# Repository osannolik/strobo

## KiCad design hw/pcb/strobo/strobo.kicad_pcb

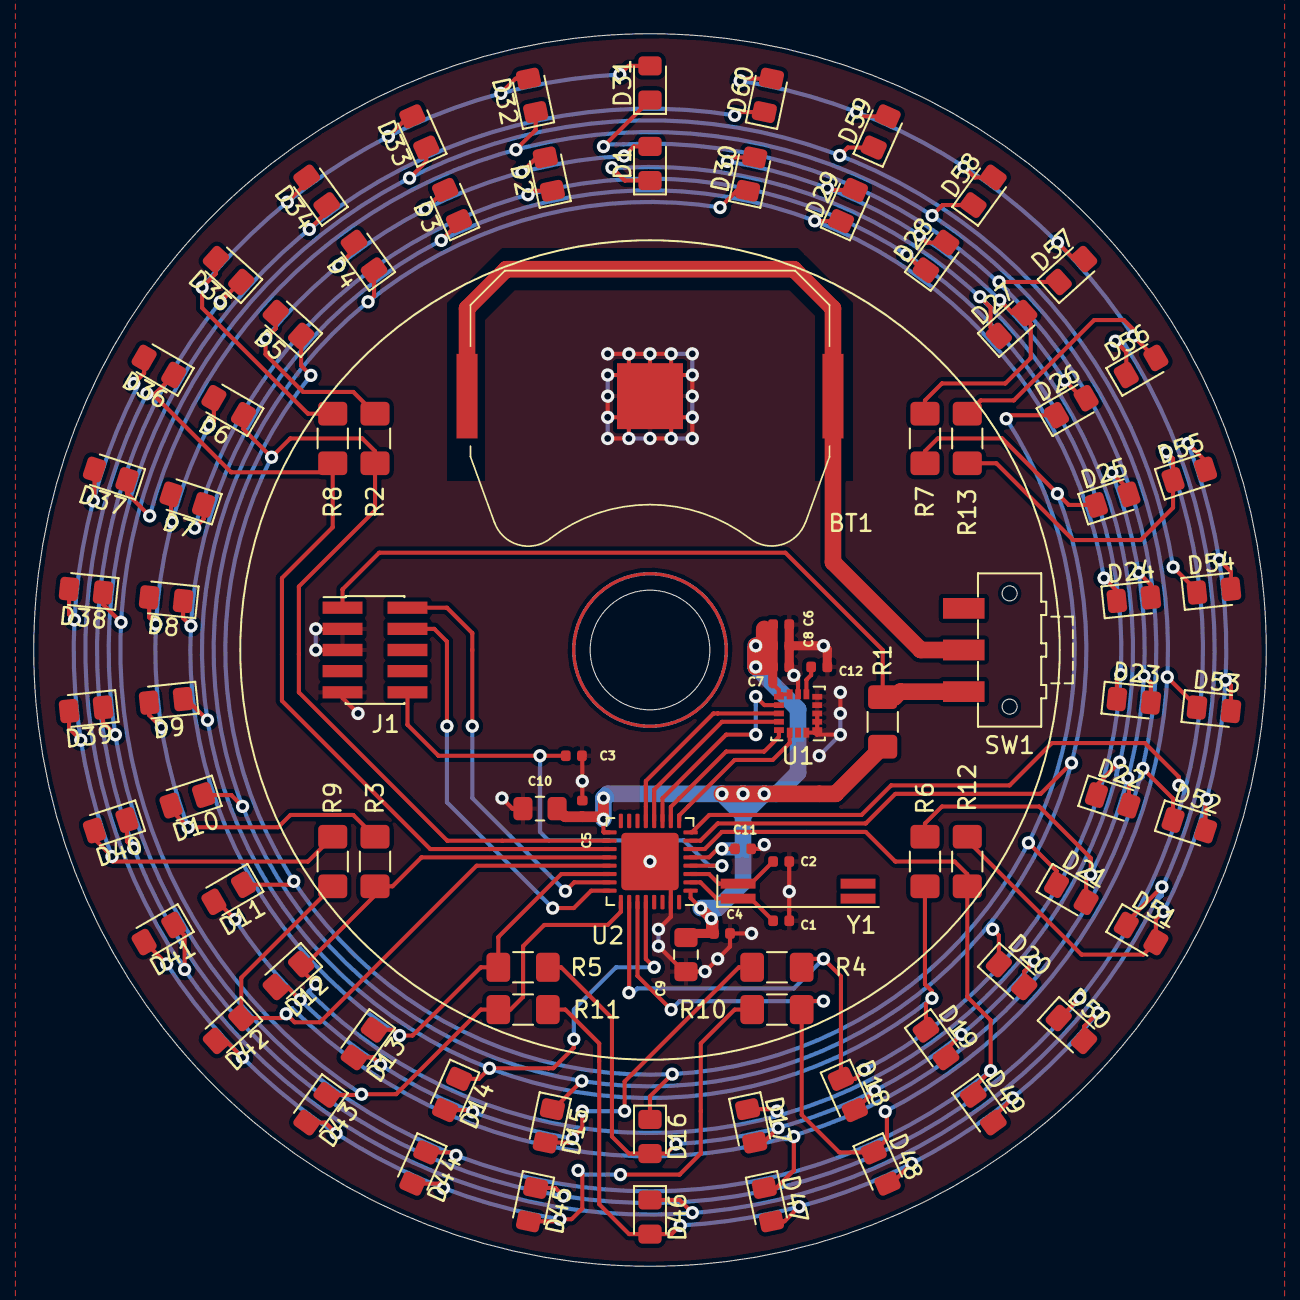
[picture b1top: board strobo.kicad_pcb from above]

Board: 2 copper layers, 74.0 x 74.0 mm, 92 parts (1 on the bottom side), 39 nets.

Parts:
BT1: Battery_Cell; BatteryHolder_Keystone_3034_1x20mm
C1, C2: 10p; C_0402_1005Metric
C3, C4, C5, C7, C8, C12: 100n; C_0402_1005Metric
C6, C11: 1u; C_0402_1005Metric
C9, C10: 22u; C_0805_2012Metric_Pad1.15x1.40mm_HandSolder
D1, D2, D3, D4, D5, D6, D7, D8, D9, D10, D11, D12, D13, D14, D15, D16, D17, D18, D19, D20, D21, D22, D23, D24, D25, D26, D27, D28, D29, D30, D31, D32, D33, D34, D35, D36, D37, D38, D39, D40, D41, D42, D43, D44, D45, D46, D47, D48, D49, D50, D51, D52, D53, D54, D55, D56, D57, D58, D59, D60: LED; LED_0805_2012Metric_Pad1.15x1.40mm_HandSolder
J1: Conn_ARM_JTAG_SWD_10; PinHeader_2x05_P1.27mm_Vertical_SMD
R1: 0R; R_1206_3216Metric_Pad1.42x1.75mm_HandSolder
R2, R3, R4, R5, R6, R7, R8, R9, R10, R11, R12, R13: 220; R_1206_3216Metric_Pad1.42x1.75mm_HandSolder
SW1: SW_SPST; SW_SPDT_CK-JS102011SAQN
U1: ICM-20602; LGA-16_3x3mm_P0.5mm_LayoutBorder3x5y
U2: STM32L051K8Ux; QFN-32-1EP_5x5mm_P0.5mm_EP3.45x3.45mm
U3: Ring_Tracks; LED_Ring
Y1: 32kHz; Crystal_SMD_SeikoEpson_MC146-4Pin_6.7x1.5mm_HandSoldering

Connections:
CLK: U1.2, U2.11
GND: BT1.2, C1.2, C2.2, C3.1, C4.2, C5.2, C6.2, C7.1, C8.2, C9.1, C10.1, C11.1, C12.2, J1.3, J1.5, J1.9, U1.8, U1.9, U1.10, U1.11, U1.12, U1.13, U1.15, U2.31, U2.33
INT: U1.6, U2.9
MISO: U1.4, U2.12
MOSI: U1.3, U2.13
NRST: C3.2, J1.10, U2.4
unnamed: BT1.1, SW1.2
unnamed: C1.1, U2.2, Y1.1
unnamed: C2.1, U2.3, Y1.4
unnamed: C4.1, C5.1, C6.1, C7.2, C8.1, C9.2, C10.2, C11.2, R1.2, U1.1, U1.16, U2.1, U2.5, U2.17
unnamed: C12.1, U1.14
unnamed: D1.2, D2.2, D3.2, D4.2, D5.2, R2.2, U3.19
unnamed: D6.2, D7.2, D8.2, D9.2, D10.2, R3.2, U3.21
unnamed: D11.2, D12.2, D13.2, D14.2, D15.2, R4.2, U3.23
unnamed: D16.2, D17.2, D18.2, D19.2, D20.2, R5.2, U3.17
unnamed: D21.2, D22.2, D23.2, D24.2, D25.2, R6.2, U3.15
unnamed: D26.2, D27.2, D28.2, D29.2, D30.2, R7.2, U3.7
unnamed: D31.2, D32.2, D33.2, D34.2, D35.2, R8.2, U3.20
unnamed: D36.2, D37.2, D38.2, D39.2, D40.2, R9.2, U3.22
unnamed: D41.2, D42.2, D43.2, D44.2, D45.2, R10.2, U3.24
unnamed: D46.2, D47.2, D48.2, D49.2, D50.2, R11.2, U3.18
unnamed: D51.2, D52.2, D53.2, D54.2, D55.2, R12.2, U3.16
unnamed: D56.2, D57.2, D58.2, D59.2, D60.2, R13.2, U3.14
RA: D6.1, D11.1, D16.1, D21.1, D26.1, R2.1, U2.18, U3.1
RB: D1.1, D12.1, D17.1, D22.1, D27.1, R3.1, U2.20, U3.6
RC: D2.1, D7.1, D18.1, D23.1, D28.1, R4.1, U2.26, U3.5
RD: D3.1, D8.1, D13.1, D24.1, D29.1, R5.1, U2.22, U3.4
RE: D4.1, D9.1, D14.1, D19.1, D30.1, R6.1, U2.28, U3.3
RF: D5.1, D10.1, D15.1, D20.1, D25.1, R7.1, U2.7, U3.2
SA: D36.1, D41.1, D46.1, D51.1, D56.1, R8.1, U2.19, U3.13
SB: D31.1, D42.1, D47.1, D52.1, D57.1, R9.1, U2.21, U3.8
SC: D32.1, D37.1, D48.1, D53.1, D58.1, R10.1, U2.27, U3.9
SD: D33.1, D38.1, D43.1, D54.1, D59.1, R11.1, U2.25, U3.10
SE: D34.1, D39.1, D44.1, D49.1, D60.1, R12.1, U2.6, U3.11
SF: D35.1, D40.1, D45.1, D50.1, D55.1, R13.1, U2.8, U3.12
SWCLK: J1.4, U2.24
SWDIO: J1.2, U2.23
VDD: J1.1, R1.1, SW1.1
~CS: U1.5, U2.10

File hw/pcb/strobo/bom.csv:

Reference,Value,Digikey,Qty,Extra,Footprint,Datasheet
R2,220,CR1206-FX-2200ELFCT-ND,,"CR1206-FX-1000ELFCT-ND, CR1206-FX-3900ELFCT-ND",Resistor_SMD:R_1206_3216Metric_Pad1.42x1.75mm_HandSolder,~
R3,220,,,,Resistor_SMD:R_1206_3216Metric_Pad1.42x1.75mm_HandSolder,~
R4,220,,,,Resistor_SMD:R_1206_3216Metric_Pad1.42x1.75mm_HandSolder,~
R5,220,,,,Resistor_SMD:R_1206_3216Metric_Pad1.42x1.75mm_HandSolder,~
R6,220,,,,Resistor_SMD:R_1206_3216Metric_Pad1.42x1.75mm_HandSolder,~
R7,220,,,,Resistor_SMD:R_1206_3216Metric_Pad1.42x1.75mm_HandSolder,~
R8,220,,,,Resistor_SMD:R_1206_3216Metric_Pad1.42x1.75mm_HandSolder,~
R9,220,,,,Resistor_SMD:R_1206_3216Metric_Pad1.42x1.75mm_HandSolder,~
R10,220,,,,Resistor_SMD:R_1206_3216Metric_Pad1.42x1.75mm_HandSolder,~
R11,220,,,,Resistor_SMD:R_1206_3216Metric_Pad1.42x1.75mm_HandSolder,~
R12,220,,,,Resistor_SMD:R_1206_3216Metric_Pad1.42x1.75mm_HandSolder,~
R13,220,,,,Resistor_SMD:R_1206_3216Metric_Pad1.42x1.75mm_HandSolder,~
R1,0R,CR1206-J/-000ELFCT-ND,,,Resistor_SMD:R_1206_3216Metric_Pad1.42x1.75mm_HandSolder,~
C5,100n,,,,Capacitor_SMD:C_0402_1005Metric,~
C4,100n,,,,Capacitor_SMD:C_0402_1005Metric,~
C3,100n,,,,Capacitor_SMD:C_0402_1005Metric,~
C7,100n,,,,Capacitor_SMD:C_0402_1005Metric,~
C8,100n,,,,Capacitor_SMD:C_0402_1005Metric,~
C12,100n,,,,Capacitor_SMD:C_0402_1005Metric,~
C1,10p,399-7746-1-ND,,,Capacitor_SMD:C_0402_1005Metric,~
C2,10p,,,,Capacitor_SMD:C_0402_1005Metric,~
C11,1u,,,,Capacitor_SMD:C_0402_1005Metric,~
C6,1u,,,,Capacitor_SMD:C_0402_1005Metric,~
C9,22u,,,,Capacitor_SMD:C_0805_2012Metric_Pad1.15x1.40mm_HandSolder,~
C10,22u,,,,Capacitor_SMD:C_0805_2012Metric_Pad1.15x1.40mm_HandSolder,~
Y1,32kHz,SER4301CT-ND,,,Crystal:Crystal_SMD_SeikoEpson_MC146-4Pin_6.7x1.5mm_HandSoldering,~
BT1,Battery_Cell,36-3034-ND,,,Battery:BatteryHolder_Keystone_3034_1x20mm,~
J1,Conn_ARM_JTAG_SWD_10,SAM1161-05-ND,,,Connector_PinHeader_1.27mm:PinHeader_2x05_P1.27mm_Vertical_SMD,http://infocenter.arm.com/help/topic/com.arm.doc.ddi0314h/DD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
U1,ICM-20602,1428-1060-1-ND,,,Package_LGA:LGA-16_3x3mm_P0.5mm_LayoutBorder3x5y,http://www.invensense.com/wp-content/uploads/2016/10/DS-0001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
D6,LED,475-2488-1-ND,100,,LED_SMD:LED_0805_2012Metric_Pad1.15x1.40mm_HandSolder,~
D11,LED,,,,LED_SMD:LED_0805_2012Metric_Pad1.15x1.40mm_HandSolder,~
D2,LED,,,,LED_SMD:LED_0805_2012Metric_Pad1.15x1.40mm_HandSolder,~
D1,LED,,,,LED_SMD:LED_0805_2012Metric_Pad1.15x1.40mm_HandSolder,~
D7,LED,,,,LED_SMD:LED_0805_2012Metric_Pad1.15x1.40mm_HandSolder,~
D12,LED,,,,LED_SMD:LED_0805_2012Metric_Pad1.15x1.40mm_HandSolder,~
D3,LED,,,,LED_SMD:LED_0805_2012Metric_Pad1.15x1.40mm_HandSolder,~
D8,LED,,,,LED_SMD:LED_0805_2012Metric_Pad1.15x1.40mm_HandSolder,~
D13,LED,,,,LED_SMD:LED_0805_2012Metric_Pad1.15x1.40mm_HandSolder,~
D18,LED,,,,LED_SMD:LED_0805_2012Metric_Pad1.15x1.40mm_HandSolder,~
D17,LED,,,,LED_SMD:LED_0805_2012Metric_Pad1.15x1.40mm_HandSolder,~
D16,LED,,,,LED_SMD:LED_0805_2012Metric_Pad1.15x1.40mm_HandSolder,~
D19,LED,,,,LED_SMD:LED_0805_2012Metric_Pad1.15x1.40mm_HandSolder,~
D14,LED,,,,LED_SMD:LED_0805_2012Metric_Pad1.15x1.40mm_HandSolder,~
D9,LED,,,,LED_SMD:LED_0805_2012Metric_Pad1.15x1.40mm_HandSolder,~
D4,LED,,,,LED_SMD:LED_0805_2012Metric_Pad1.15x1.40mm_HandSolder,~
D24,LED,,,,LED_SMD:LED_0805_2012Metric_Pad1.15x1.40mm_HandSolder,~
D23,LED,,,,LED_SMD:LED_0805_2012Metric_Pad1.15x1.40mm_HandSolder,~
D22,LED,,,,LED_SMD:LED_0805_2012Metric_Pad1.15x1.40mm_HandSolder,~
D21,LED,,,,LED_SMD:LED_0805_2012Metric_Pad1.15x1.40mm_HandSolder,~
D25,LED,,,,LED_SMD:LED_0805_2012Metric_Pad1.15x1.40mm_HandSolder,~
D20,LED,,,,LED_SMD:LED_0805_2012Metric_Pad1.15x1.40mm_HandSolder,~
D15,LED,,,,LED_SMD:LED_0805_2012Metric_Pad1.15x1.40mm_HandSolder,~
D10,LED,,,,LED_SMD:LED_0805_2012Metric_Pad1.15x1.40mm_HandSolder,~
D5,LED,,,,LED_SMD:LED_0805_2012Metric_Pad1.15x1.40mm_HandSolder,~
D30,LED,,,,LED_SMD:LED_0805_2012Metric_Pad1.15x1.40mm_HandSolder,~
D29,LED,,,,LED_SMD:LED_0805_2012Metric_Pad1.15x1.40mm_HandSolder,~
D28,LED,,,,LED_SMD:LED_0805_2012Metric_Pad1.15x1.40mm_HandSolder,~
D27,LED,,,,LED_SMD:LED_0805_2012Metric_Pad1.15x1.40mm_HandSolder,~
D26,LED,,,,LED_SMD:LED_0805_2012Metric_Pad1.15x1.40mm_HandSolder,~
D36,LED,,,,LED_SMD:LED_0805_2012Metric_Pad1.15x1.40mm_HandSolder,~
D41,LED,,,,LED_SMD:LED_0805_2012Metric_Pad1.15x1.40mm_HandSolder,~
D32,LED,,,,LED_SMD:LED_0805_2012Metric_Pad1.15x1.40mm_HandSolder,~
D31,LED,,,,LED_SMD:LED_0805_2012Metric_Pad1.15x1.40mm_HandSolder,~
D37,LED,,,,LED_SMD:LED_0805_2012Metric_Pad1.15x1.40mm_HandSolder,~
D42,LED,,,,LED_SMD:LED_0805_2012Metric_Pad1.15x1.40mm_HandSolder,~
D33,LED,,,,LED_SMD:LED_0805_2012Metric_Pad1.15x1.40mm_HandSolder,~
D38,LED,,,,LED_SMD:LED_0805_2012Metric_Pad1.15x1.40mm_HandSolder,~
D43,LED,,,,LED_SMD:LED_0805_2012Metric_Pad1.15x1.40mm_HandSolder,~
D48,LED,,,,LED_SMD:LED_0805_2012Metric_Pad1.15x1.40mm_HandSolder,~
D47,LED,,,,LED_SMD:LED_0805_2012Metric_Pad1.15x1.40mm_HandSolder,~
D46,LED,,,,LED_SMD:LED_0805_2012Metric_Pad1.15x1.40mm_HandSolder,~
D49,LED,,,,LED_SMD:LED_0805_2012Metric_Pad1.15x1.40mm_HandSolder,~
D44,LED,,,,LED_SMD:LED_0805_2012Metric_Pad1.15x1.40mm_HandSolder,~
D39,LED,,,,LED_SMD:LED_0805_2012Metric_Pad1.15x1.40mm_HandSolder,~
D34,LED,,,,LED_SMD:LED_0805_2012Metric_Pad1.15x1.40mm_HandSolder,~
D54,LED,,,,LED_SMD:LED_0805_2012Metric_Pad1.15x1.40mm_HandSolder,~
D53,LED,,,,LED_SMD:LED_0805_2012Metric_Pad1.15x1.40mm_HandSolder,~
D52,LED,,,,LED_SMD:LED_0805_2012Metric_Pad1.15x1.40mm_HandSolder,~
D51,LED,,,,LED_SMD:LED_0805_2012Metric_Pad1.15x1.40mm_HandSolder,~
D55,LED,,,,LED_SMD:LED_0805_2012Metric_Pad1.15x1.40mm_HandSolder,~
D50,LED,,,,LED_SMD:LED_0805_2012Metric_Pad1.15x1.40mm_HandSolder,~
D45,LED,,,,LED_SMD:LED_0805_2012Metric_Pad1.15x1.40mm_HandSolder,~
D40,LED,,,,LED_SMD:LED_0805_2012Metric_Pad1.15x1.40mm_HandSolder,~
D35,LED,,,,LED_SMD:LED_0805_2012Metric_Pad1.15x1.40mm_HandSolder,~
D60,LED,,,,LED_SMD:LED_0805_2012Metric_Pad1.15x1.40mm_HandSolder,~
D59,LED,,,,LED_SMD:LED_0805_2012Metric_Pad1.15x1.40mm_HandSolder,~
D58,LED,,,,LED_SMD:LED_0805_2012Metric_Pad1.15x1.40mm_HandSolder,~
D57,LED,,,,LED_SMD:LED_0805_2012Metric_Pad1.15x1.40mm_HandSolder,~
D56,LED,,,,LED_SMD:LED_0805_2012Metric_Pad1.15x1.40mm_HandSolder,~
U3,Ring_Tracks,,,,strobo:LED_Ring,
U2,STM32L051K8Ux,,,,Package_DFN_QFN:QFN-32-1EP_5x5mm_P0.5mm_EP3.45x3.45mm,http://www.st.com/st-web-ui/static/active/en/resource/techni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
SW1,SW_SPST,401-1999-1-ND,,,Button_Switch_SMD:SW_SPDT_CK-JS102011SAQN,~

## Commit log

2019-08-09 power for mcu and mems
2019-08-09 Some datasheets
2019-08-16 leds 12 deg sep
2019-08-18 debug connector
2019-08-21 charlieplexed leds
2019-08-27 footprints
2019-08-28 Add net list
2019-08-28 pcb from scratch
2019-08-28 initial led placement
2019-08-30 led tracks for inner ring
2019-08-31 outer ring
2019-08-31 map ring tracks to schematic
2019-09-01 major routing
2019-09-01 move imu and pour gnd
2019-09-01 cosmetics, ref placement etc
2019-09-01 gerber output rev a1
2019-10-06 rust template project
2019-10-10 pin 2 and 3 of oscillator should be nc...
2019-10-13 Blink that LED!
2019-10-16 Very inaccurate strobing due to overhead in isr?
2019-10-21 Upgrade to RTFM 0.5.0-beta. Temporarily use local pac.
2019-10-22 Oops, missing files.
2019-10-27 charlieplexing test
